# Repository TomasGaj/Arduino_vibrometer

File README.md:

# Arduino UNO contactless vibrometer

**UPDATE 29-07-2023: I've squized Arduino and MPC3008 to the maximum, in the meanwhile
I didn't continue in C# as I optimized Arduino otput data format, see:** [Arduino_Nano_MPC3008_logger](https://github.com/TomasGaj/Arduino_Nano_MPC3008_logger)

## General Introduction

It's expansion board for Arduino UNO.
Vibrometer is based on TCRT5000 IR sensor and MCP3008 adc.
I used KiCAD 6.0.
It's tested and working.
Arduino is used only to send out ADC values together with time stamps.
C# application is coming.
Up to now I was not able to eliminate noise comping from USB supply (50 Hz), so I use 9V battery to supply power to the circuit.

## Physical principle

It's light intensity distance sensor. The closer the object is, the more light is reflected back to phototransistor.
However, the correct distance of vibrating object can not be measured without calibration. I hope I'll solve later.
Working distance is 15-25 mm.

## Arduino code

I use this SW library:
[Fast MCP3008 library for Arduino Uno](https://github.com/arithmechanics/fast-MCP3008)

I modified the original code, I am sending out data in this format:

**ADC VALUE** (hex, 10-bit adc) ***(space)*** **MICRO-SECONDS** (hex, result of Arduino function ***micros()***)

## Electrical circuit
**Signal path:**

Signal -> High pass filter -> Low pass filter -> Amplifier -> Level shifter -> ADC (here MCP3008) -> Arduino Uno

**My electrical design is inspired by:**

[Matiss Malahs - Design of a Low Cost Laser Vibrometer System](https://www.theseus.fi/handle/10024/89919)

[Heart Rate Measurement using PPG](http://www.ee.iitb.ac.in/~stallur/wp-content/uploads/2017/02/Heart-Rate-Measurement-using-PPG1.pdf)

## Details of the electrical circuit
I needed to do adjustments:
   - high pass filter is calculater fc = 4.82 Hz
   - high pass is also removing away DC part of the signal
   - low pass is calculated fc = 796 Hz
   - **everythnig above 200Hz looks ugly with actual data acqusition speed**
   - TestPoint 1 - direct output from phototransistor (proportional to light intensity)
   - TestPoint 2 - voltage after high pass filter
   - TestPoint 3 - voltage after low pass filter
   - TestPoint 4 - voltage after amplification
   - TestPoint 5 - signal before entering ADC
   - TestPoint 6 - ground
   
## Next steps

  - testing and testing...
  - speed up Arduino code
  - eliminate 9V battery
  - finish C# app
  - thinking about ARM processor (now testing RPi)
  - thinking about more complicated physical principle (planning intensity modulation tests, reading about self-mixing)

**More about testing and other details:**

[sensorsplayground.com](http://www.sensorsplayground.com/)

Enjoy!

Tomas Gajdarus

tomas (dot) gajdarus (at) seznam (dot) cz

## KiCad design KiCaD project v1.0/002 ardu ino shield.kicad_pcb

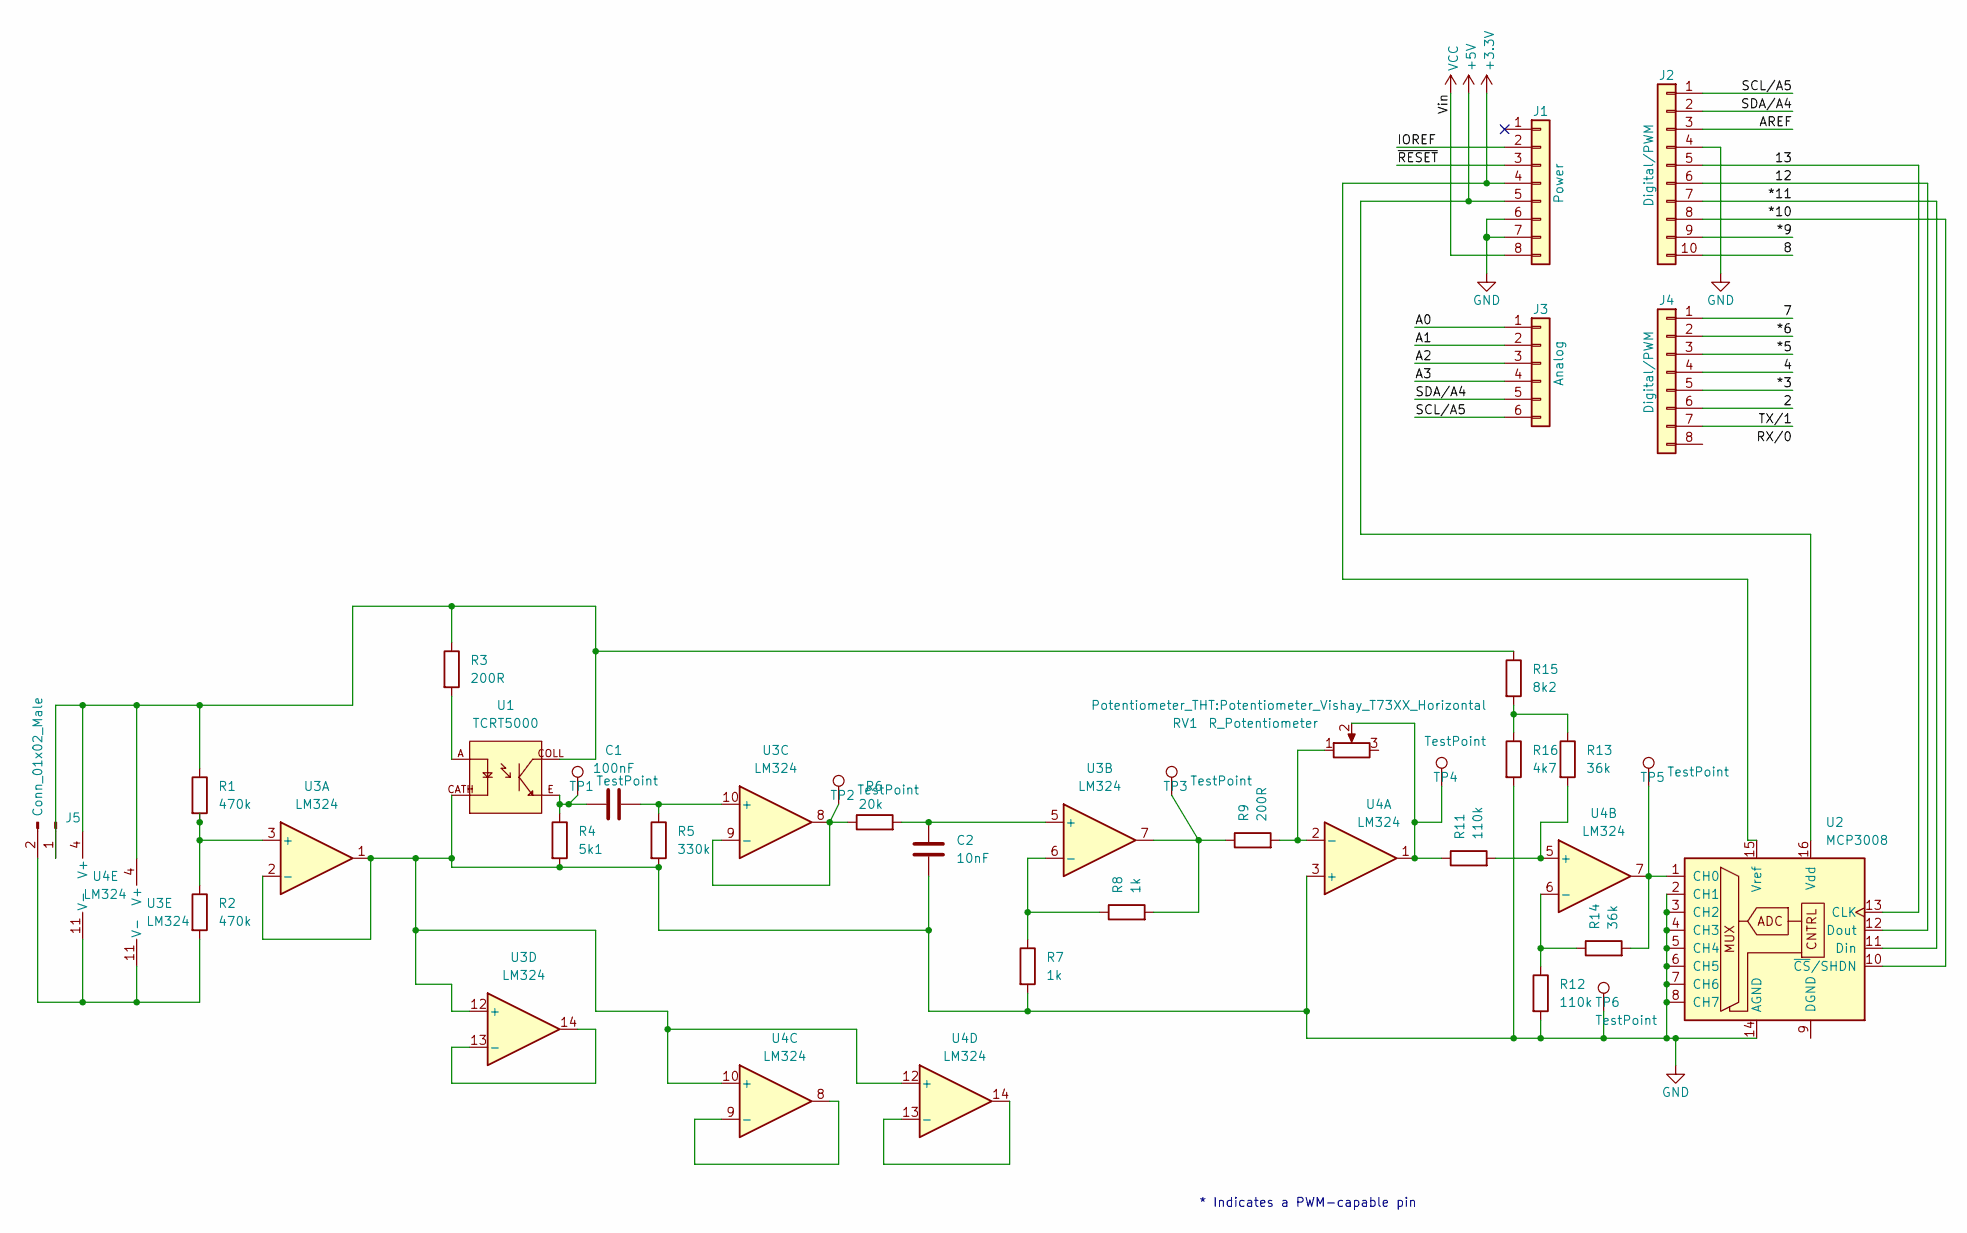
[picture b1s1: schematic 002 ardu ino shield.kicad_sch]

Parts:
C1: 100nF; C_0603_1608Metric_Pad1.08x0.95mm_HandSolder
C2: 10nF; C_0603_1608Metric_Pad1.08x0.95mm_HandSolder
J1: Power; PinHeader_1x08_P2.54mm_Vertical
J2: Digital/PWM; PinHeader_1x10_P2.54mm_Vertical
J3: Analog; PinHeader_1x06_P2.54mm_Vertical
J4: Digital/PWM; PinHeader_1x08_P2.54mm_Vertical
J5: Conn_01x02_Male; PinHeader_1x02_P2.54mm_Vertical
R1, R2: 470k; R_0603_1608Metric_Pad0.98x0.95mm_HandSolder
R3, R9: 200R; R_0603_1608Metric_Pad0.98x0.95mm_HandSolder
R4: 5k1; R_0603_1608Metric_Pad0.98x0.95mm_HandSolder
R5: 330k; R_0603_1608Metric_Pad0.98x0.95mm_HandSolder
R6: 20k; R_0603_1608Metric_Pad0.98x0.95mm_HandSolder
R7, R8: 1k; R_0603_1608Metric_Pad0.98x0.95mm_HandSolder
R11, R12: 110k; R_0603_1608Metric_Pad0.98x0.95mm_HandSolder
R13, R14: 36k; R_0603_1608Metric_Pad0.98x0.95mm_HandSolder
R15: 8k2; R_0603_1608Metric_Pad0.98x0.95mm_HandSolder
R16: 4k7; R_0603_1608Metric_Pad0.98x0.95mm_HandSolder
RV1: R_Potentiometer; Potentiometer_Vishay_T73XX_Horizontal
TP1, TP2, TP3, TP4, TP5, TP6: TestPoint; Pin_D0.9mm_L10.0mm_W2.4mm_FlatFork
U1: TCRT5000; OPTO_TCRT5000; PARTREV 1.7
U2: MCP3008; SOIC127P600X175-16N
U3, U4: LM324; SOIC127P600X175-14N

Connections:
+3V3: J1.4, U2.15 (Vref)
+5V: J1.5, U2.16 (Vdd)
/2: J4.6
/4: J4.4
/7: J4.1
/8: J2.10
/12: J2.6, U2.12 (Dout)
/13: J2.5, U2.13 (CLK)
/*3: J4.5
/*5: J4.3
/*6: J4.2
/*9: J2.9
/*10: J2.8, U2.10 (~CS/SHDN)
/*11: J2.7, U2.11 (Din)
/A0: J3.1
/A1: J3.2
/A2: J3.3
/A3: J3.4
/AREF: J2.3
/IOREF: J1.2
/SCL/A5: J2.1, J3.6
/SDA/A4: J2.2, J3.5
/TX/1: J4.7
/~RESET: J1.3
GND: C2.1, J1.6, J1.7, J2.4, R4.2, R5.2, R7.2, R12.2, R16.2, TP6.1, U1.CATH, U2.2 (CH1), U2.3 (CH2), U2.4 (CH3), U2.5 (CH4), U2.6 (CH5), U2.7 (CH6), U2.8 (CH7), U2.14 (AGND), U3.1, U3.2 (-), U3.12 (+), U4.3 (+), U4.10 (+), U4.12 (+)
unnamed: C1.1, R4.1, TP1.1, U1.E
unnamed: C1.2, R5.1, U3.10 (+)
unnamed: C2.2, R6.2, U3.5 (+)
unnamed: J5.1, R1.1, R3.1, R15.1, U1.COLL, U3.4 (V+), U4.4 (V+)
unnamed: J5.2, R2.2, U3.11 (V-), U4.11 (V-)
unnamed: R1.2, R2.1, U3.3 (+)
unnamed: R3.2, U1.A
unnamed: R6.1, TP2.1, U3.8, U3.9 (-)
unnamed: R7.1, R8.1, U3.6 (-)
unnamed: R8.2, R9.1, TP3.1, U3.7
unnamed: R9.2, RV1.1, U4.2 (-)
unnamed: R11.1, RV1.2, TP4.1, U4.1
unnamed: R11.2, R13.2, U4.5 (+)
unnamed: R12.1, R14.1, U4.6 (-)
unnamed: R13.1, R15.2, R16.1
unnamed: R14.2, TP5.1, U2.1 (CH0), U4.7
unnamed: U3.13 (-), U3.14
unnamed: U4.8, U4.9 (-)
unnamed: U4.13 (-), U4.14
VCC: J1.8

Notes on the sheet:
* Indicates a PWM-capable pin

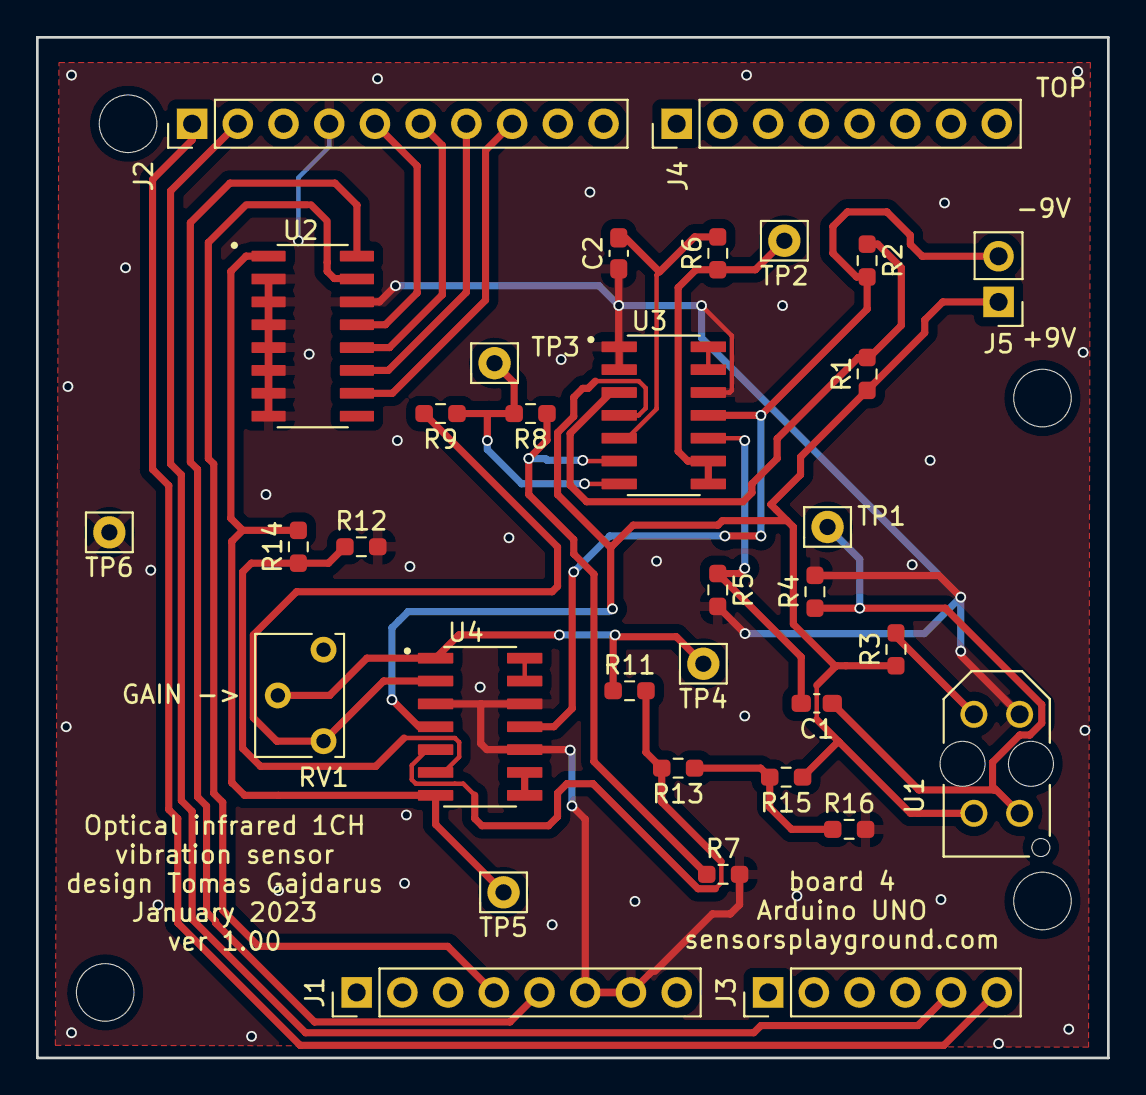
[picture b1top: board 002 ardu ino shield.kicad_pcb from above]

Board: 2 copper layers, 59.5 x 56.7 mm, 37 parts (0 on the bottom side), 28 nets.

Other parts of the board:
MH1, MH2, MH3, MH4: MountingHole_3.2mm
